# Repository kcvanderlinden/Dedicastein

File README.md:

A espresso machine can't be that complicated, can it?

# WARNING
This is an ongoing project which has not been fully tested. (re) Use at your own risk.

# AIM
replacing the board of a Delonghi Dedica EC685 with a Raspberry pico.

# TRAIN-OF-THOUGHT
- The GAGGUINO project designed for GAGGIA CLASSIC is a project that makes the espresso machine smart by adding some sensors and controllers. 
- A Dedica is not so different from a GAGGIA CLASSIC: it uses the same pump and uses a simalair heating method.
- An espresso machine in its core is quite simple, such as a Flair. Water needs to heat to a certain point and the pump needs to be powered.
- The heating block and the pump are both 230v.
- Arduino and Pico are designed to control switches and read sensors.
- I need a challenge for in this afwull winter time.
- Being able to add extra sensors and controllers (such as an AC dimmer), enables for more espresso profiling.
- Thinkering with stuff is huge fun.

# CHECKLIST
- [x] Reading the temprature with the termoster 
- [x] Turning the heating block on and off
- [x] PID temprature control
- [x] Turning the pump on and off
- [x] Pump power control (AC dimmer)
- [ ] Reading the flow sensor
- [ ] Implement the steam wand
- [x] Read the front buttons and control the LEDs

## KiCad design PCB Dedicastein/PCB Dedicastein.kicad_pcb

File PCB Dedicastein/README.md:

These schematics are of an untested prototype. So far I have tested the individual components using a breadboard. This worked using the code. I then created the schematic with KiCad and have printed it. I have yet to buy the parts, create the board and test it. 

Recreate at your own risk as it uses main voltage.

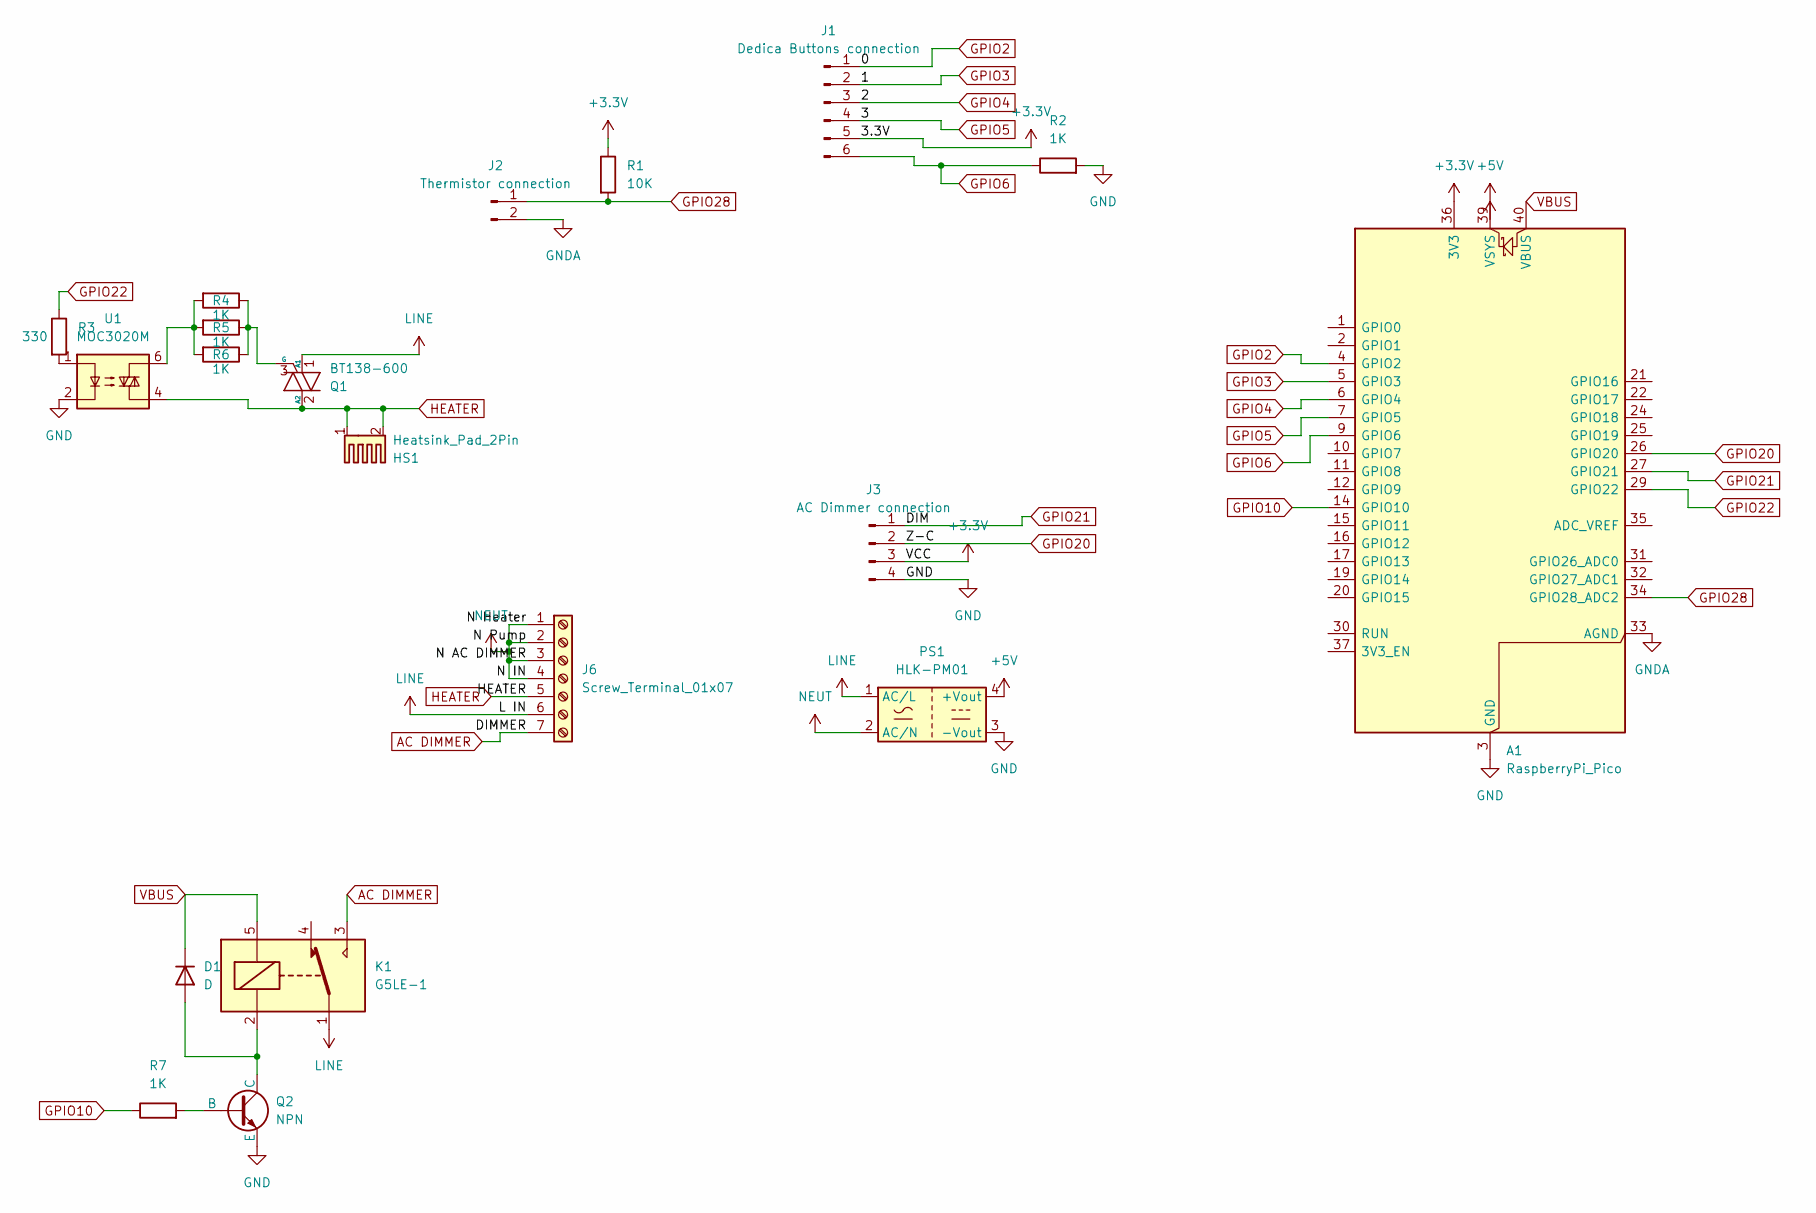
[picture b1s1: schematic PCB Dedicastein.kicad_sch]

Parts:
A1: RaspberryPi_Pico; RaspberryPi_Pico_Common_THT_MountingHoles
D1: D; D_A-405_P7.62mm_Horizontal
HS1: Heatsink_Pad_2Pin; Heatsink_Fischer_SK104-STC-STIC_35x13mm_2xDrill2.5mm
J1: Dedica Buttons connection; PinSocket_1x06_P2.54mm_Vertical
J2: Thermistor connection; PinSocket_1x02_P2.54mm_Vertical
J3: AC Dimmer connection; PinSocket_1x04_P2.54mm_Vertical
J6: Screw_Terminal_01x07; Altech_AK100_1x07_P5.00mm
K1: G5LE-1; Relay_SPDT_Omron-G5LE-1
PS1: HLK-PM01; Converter_ACDC_Hi-Link_HLK-PMxx
Q1: BT138-600; TO-220-3_Vertical
Q2: NPN; 3-LEADTO-92BULK
R1: 10K; R_Axial_DIN0204_L3.6mm_D1.6mm_P5.08mm_Horizontal
R2, R4, R5, R6, R7: 1K; R_Axial_DIN0204_L3.6mm_D1.6mm_P5.08mm_Horizontal
R3: 330; R_Axial_DIN0204_L3.6mm_D1.6mm_P5.08mm_Horizontal
U1: MOC3020M; DIP762W51P254L851H508Q6N

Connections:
+3.3V: A1.36 (3V3), J1.5, J3.3, R1.1
+5V: A1.39 (VSYS), PS1.4 (+Vout)
AC DIMMER: J6.7, K1.3
GND: A1.3 (GND), A1.8 (GND), A1.13 (GND), A1.18 (GND), A1.23 (GND), A1.28 (GND), A1.38 (GND), J3.4, PS1.3 (-Vout), Q2.3 (E), R2.2, U1.2
GNDA: A1.33 (AGND), J2.2
GPIO2: A1.4 (GPIO2), J1.1
GPIO3: A1.5 (GPIO3), J1.2
GPIO4: A1.6 (GPIO4), J1.3
GPIO5: A1.7 (GPIO5), J1.4
GPIO6: A1.9 (GPIO6), J1.6, R2.1
GPIO10: A1.14 (GPIO10), R7.1
GPIO20: A1.26 (GPIO20), J3.2
GPIO21: A1.27 (GPIO21), J3.1
GPIO22: A1.29 (GPIO22), R3.1
GPIO28: A1.34 (GPIO28_ADC2), J2.1, R1.2
HEATER: HS1.1, HS1.2, J6.5, Q1.2 (A2), U1.4
LINE: J6.6, K1.1, PS1.1 (AC/L), Q1.1 (A1)
NEUT: J6.1, J6.2, J6.3, J6.4, PS1.2 (AC/N)
unnamed: D1.2 (A), K1.2, Q2.1 (C)
unnamed: Q1.3 (G), R4.1, R5.1, R6.1
unnamed: Q2.2 (B), R7.2
unnamed: R3.2, U1.1
unnamed: R4.2, R5.2, R6.2, U1.6
VBUS: A1.40 (VBUS), D1.1 (K), K1.5

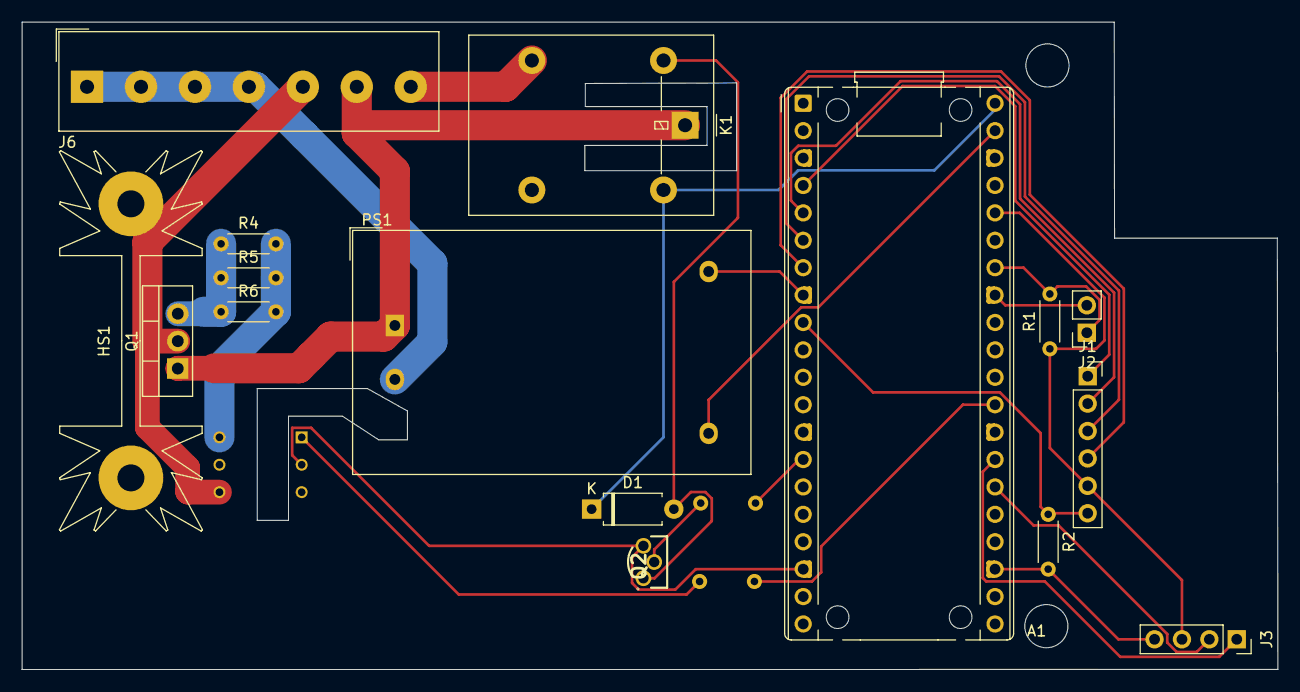
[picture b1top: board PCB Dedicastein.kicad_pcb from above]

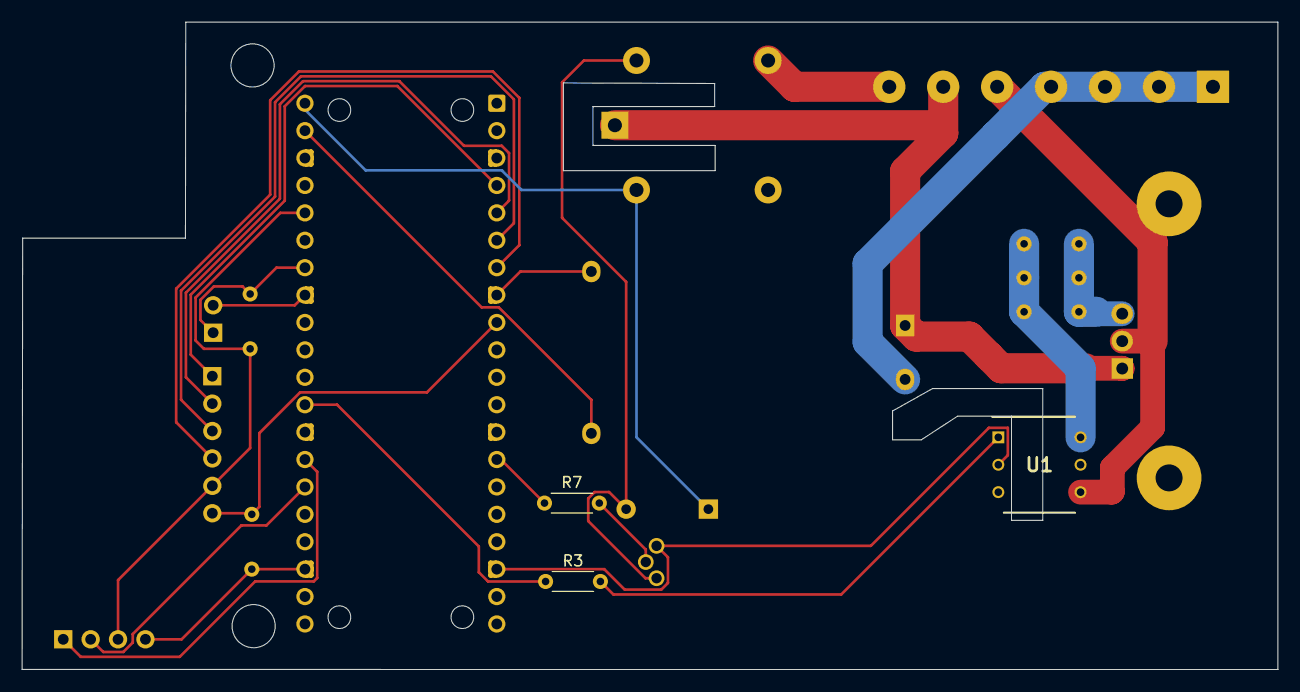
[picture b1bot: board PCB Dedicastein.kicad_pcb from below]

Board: 2 copper layers, 116.4 x 60.0 mm, 19 parts (3 on the bottom side), 24 nets.

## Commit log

2024-12-06 adding code of thermoster and readme
2024-12-06 change file extension documentation
2024-12-15 add dimmer, button and PID function
2024-12-15 update checklist and clean comments and minor details.
2025-01-05 Add PCB design for new mainboard Dedica
2025-01-05 add pictures of some prototype wiring.
2025-01-05 Add warnings for recreation while in testphase
2025-02-05 Add asyncio use for handling buttons presses and toggling relay
